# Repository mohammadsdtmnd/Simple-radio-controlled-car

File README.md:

# Simple-radio-controlled-car
Here is the hardware of RC car, including its motor driver through radio, battery pack cell balancer/protector and battery charger
System targer:
1- Two 5V 1.3A Motor drive
2- Series 4 cell battery pack with cell balancer and pack protector
3- Simple USB type C, 4 series cell Li-Ion charger

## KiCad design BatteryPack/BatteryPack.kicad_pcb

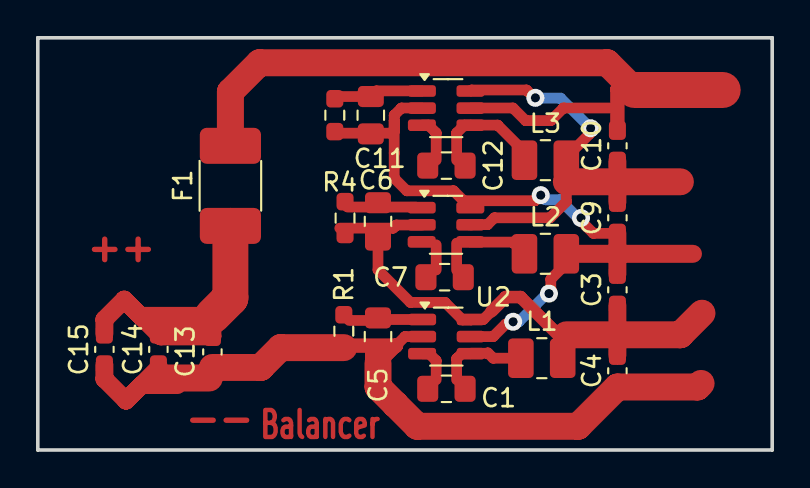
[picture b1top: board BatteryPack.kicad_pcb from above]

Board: 2 copper layers, 40.8 x 22.9 mm, 23 parts (0 on the bottom side), 15 nets.

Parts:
C1, C5, C6, C7, C11, C12: 10nF; C_0805_2012Metric_Pad1.18x1.45mm_HandSolder
C3, C4, C9, C10, C13, C14, C15: 10uF; C_0603_1608Metric_Pad1.08x0.95mm_HandSolder
F1: MF-MSMF150/24X-2; Fuse_1812_4532Metric_Pad1.30x3.40mm_HandSolder
L1, L2, L3: 2.2uH; L_1008_2520Metric_Pad1.43x2.20mm_HandSolder
R1, R4, R6: 27k; R_0603_1608Metric_Pad0.98x0.95mm_HandSolder
U2, U3, U4: ETA3000S2G; SOT-23-6_Handsoldering

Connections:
/cell+: C3.1, C4.2, C6.1, L1.2, R4.2, U2.6 (BATc), U3.2 (BATn)
/pack+: C13.2, C14.2, C15.2, F1.1
/pack-: C4.1, C5.1, C13.1, C14.1, C15.1, R1.2, U2.2 (BATn)
unnamed: C10.2, F1.2, U4.5 (BATP)
unnamed: C9.2, C10.1, L3.2, U3.5 (BATP), U4.6 (BATc)
unnamed: C3.2, C9.1, C11.1, L2.2, R6.2, U2.5 (BATP), U3.6 (BATc), U4.2 (BATn)
unnamed: C1.1, U2.3 (BIAS)
unnamed: C5.2, R1.1, U2.1 (Iset)
unnamed: C1.2, L1.1, U2.4 (SW)
unnamed: C7.1, U3.3 (BIAS)
unnamed: C6.2, R4.1, U3.1 (Iset)
unnamed: C7.2, L2.1, U3.4 (SW)
unnamed: C12.1, U4.3 (BIAS)
unnamed: C11.2, R6.1, U4.1 (Iset)
unnamed: C12.2, L3.1, U4.4 (SW)

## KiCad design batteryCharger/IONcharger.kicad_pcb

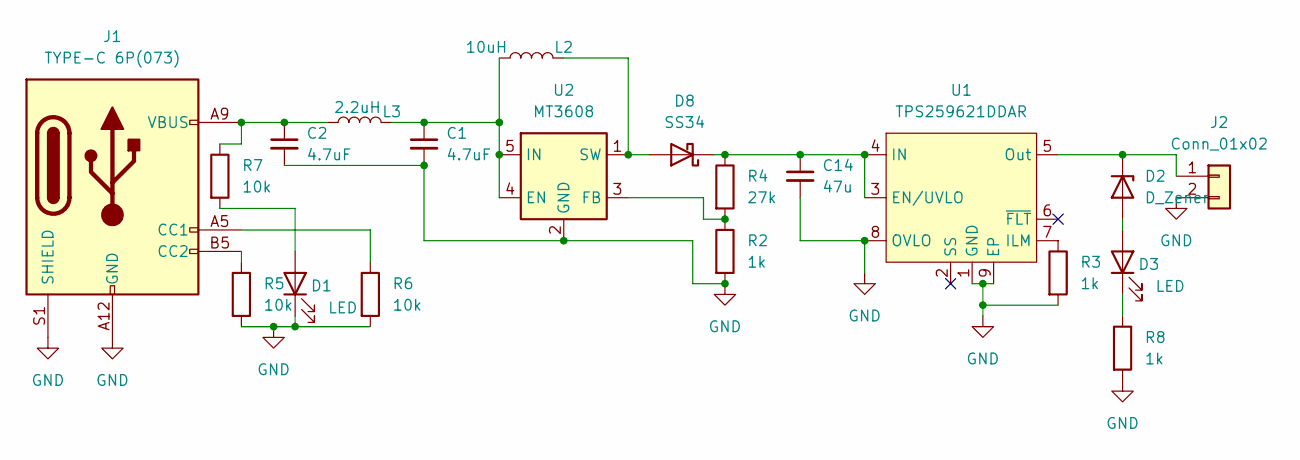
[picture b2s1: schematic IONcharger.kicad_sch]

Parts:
C1, C2: 4.7uF; C_1206_3216Metric_Pad1.33x1.80mm_HandSolder
C14: 47u; C_0805_2012Metric_Pad1.18x1.45mm_HandSolder
D1, D3: LED; LED_0805_2012Metric_Pad1.15x1.40mm_HandSolder
D2: D_Zener; D_SMA_Handsoldering
D8: SS34; D_SMA
J1: TYPE-C 6P(073); USB_C_Receptacle_HRO_TYPE-C-31-M-17
J2: Conn_01x02; SolderWire-0.5sqmm_1x02_P4.6mm_D0.9mm_OD2.1mm
L2: 10uH; L_7.3x7.3_H3.5; Partnumber TMPC0603H-100MG-D
L3: 2.2uH; L_1008_2520Metric_Pad1.43x2.20mm_HandSolder; Partnumber DFE252012F-2R2M=P2
R2, R3, R8: 1k; R_0603_1608Metric_Pad0.98x0.95mm_HandSolder
R4: 27k; R_0603_1608Metric_Pad0.98x0.95mm_HandSolder
R5, R6, R7: 10k; R_0603_1608Metric_Pad0.98x0.95mm_HandSolder
U1: TPS259621DDAR; SOIC-8-1EP_3.9x4.9mm_P1.27mm_EP2.514x3.2mm
U2: MT3608; SOT-23-6

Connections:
GND: C1.2, C2.2, C14.2, D1.1 (K), J1.A12 (GND), J1.B12 (GND), J1.S1 (SHIELD), J2.2, R2.2, R3.2, R5.2, R6.2, R8.2, U1.1 (GND), U1.8 (OVLO), U1.9 (EP), U2.2 (GND)
unnamed: C2.1, J1.A9 (VBUS), J1.B9 (VBUS), L3.1, R7.1
unnamed: D1.2 (A), R7.2
unnamed: D2.2 (A), D3.2 (A)
unnamed: D2.1 (K), J2.1, U1.5 (Out)
unnamed: D3.1 (K), R8.1
unnamed: D8.2 (A), L2.2, U2.1 (SW)
unnamed: C14.1, D8.1 (K), R4.1, U1.3 (EN/UVLO), U1.4 (IN)
unnamed: J1.A5 (CC1), R6.1
unnamed: J1.B5 (CC2), R5.1
unnamed: R3.1, U1.7 (ILM)
unnamed: C1.1, L2.1, L3.2, U2.4 (EN), U2.5 (IN)
unnamed: R2.1, R4.2, U2.3 (FB)

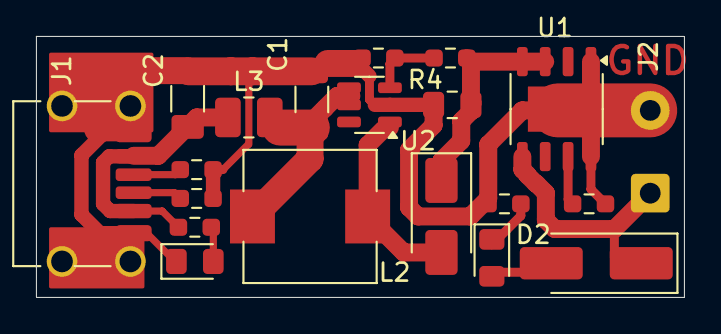
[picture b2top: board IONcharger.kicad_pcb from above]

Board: 2 copper layers, 36.0 x 14.5 mm, 20 parts (0 on the bottom side), 13 nets.

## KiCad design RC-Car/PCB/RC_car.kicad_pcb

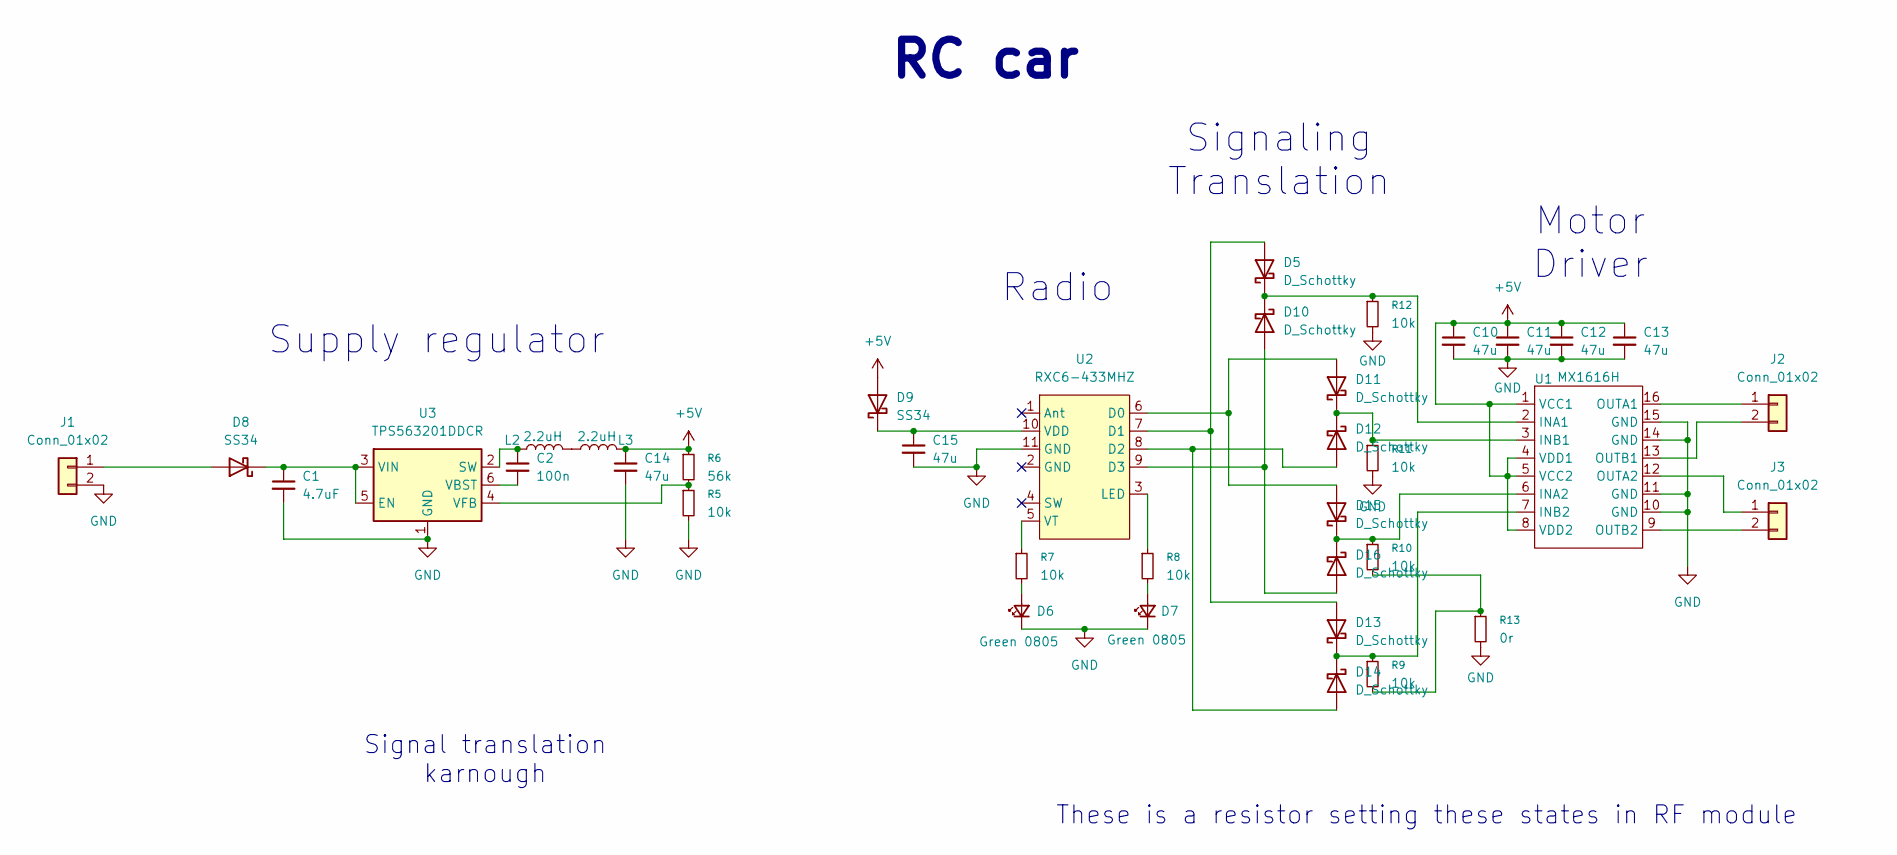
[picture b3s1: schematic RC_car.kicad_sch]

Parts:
C1: 4.7uF; C_1206_3216Metric_Pad1.33x1.80mm_HandSolder
C2: 100n; C_0603_1608Metric_Pad1.08x0.95mm_HandSolder
C10, C11, C12, C13, C14, C15: 47u; C_0805_2012Metric_Pad1.18x1.45mm_HandSolder
D5, D10, D11, D12, D13, D14, D15, D16: D_Schottky; D_SOD-123F_HandSoldering
D6, D7: Green 0805; LED_0805_2012Metric_Pad1.15x1.40mm_HandSolder
D8, D9: SS34; D_SMA
J1, J2, J3: Conn_01x02; SolderWire-0.5sqmm_1x02_P4.6mm_D0.9mm_OD2.1mm
L2, L3: 2.2uH; L_1008_2520Metric_Pad1.43x2.20mm_HandSolder; Partnumber DFE252012F-2R2M=P2
R5, R7, R8, R9, R10, R11, R12: 10k; R_0603_1608Metric_Pad0.98x0.95mm_HandSolder
R6: 56k; R_0603_1608Metric_Pad0.98x0.95mm_HandSolder
R13: 0r; R_1206_3216Metric_Pad1.30x1.75mm_HandSolder
U1: MX1616H; SOP-16_3.9x9.9mm_P1.27mm
U2: RXC6-433MHZ
U3: TPS563201DDCR; SOT-23-6

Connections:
+5V: C10.1, C11.1, C12.1, C13.1, C14.1, D9.2 (A), L3.2, R6.1, U1.1 (VCC1), U1.4 (VDD1), U1.5 (VCC2), U1.8 (VDD2)
GND: C1.2, C10.2, C11.2, C12.2, C13.2, C14.2, C15.2, D6.1 (K), D7.1 (K), J1.2, R5.2, R11.2, R12.2, R13.2, U1.10 (GND), U1.11 (GND), U1.14 (GND), U1.15 (GND), U2.11 (GND), U3.1 (GND)
unnamed: D6.2 (A), R7.2
unnamed: D7.2 (A), R8.2
unnamed: D8.2 (A), J1.1
unnamed: C1.1, D8.1 (K), U3.3 (VIN), U3.5 (EN)
unnamed: C15.1, D9.1 (K), U2.10 (VDD)
unnamed: D10.2 (A), D16.2 (A), U2.9 (D3)
unnamed: D5.1 (K), D10.1 (K), R12.1, U1.2 (INA1)
unnamed: D11.2 (A), D15.2 (A), U2.6 (D0)
unnamed: D11.1 (K), D12.1 (K), R11.1, U1.3 (INB1)
unnamed: D12.2 (A), D14.2 (A), U2.8 (D2)
unnamed: D5.2 (A), D13.2 (A), U2.7 (D1)
unnamed: D13.1 (K), D14.1 (K), R9.1, U1.7 (INB2)
unnamed: D15.1 (K), D16.1 (K), R10.1, U1.6 (INA2)
unnamed: J2.1, U1.16 (OUTA1)
unnamed: J2.2, U1.13 (OUTB1)
unnamed: J3.1, U1.12 (OUTA2)
unnamed: J3.2, U1.9 (OUTB2)
unnamed: L2.2, L3.1
unnamed: R9.2, R10.2, R13.1
unnamed: R8.1, U2.3 (LED)
unnamed: R7.1, U2.5 (VT)
unnamed: C2.1, L2.1, U3.2 (SW)
unnamed: C2.2, U3.6 (VBST)
unnamed: R5.1, R6.2, U3.4 (VFB)

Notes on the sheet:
Signal translation karnough
Motor Driver
RC car
Signaling Translation
These is a resistor setting these states in RF module
Radio
Supply regulator

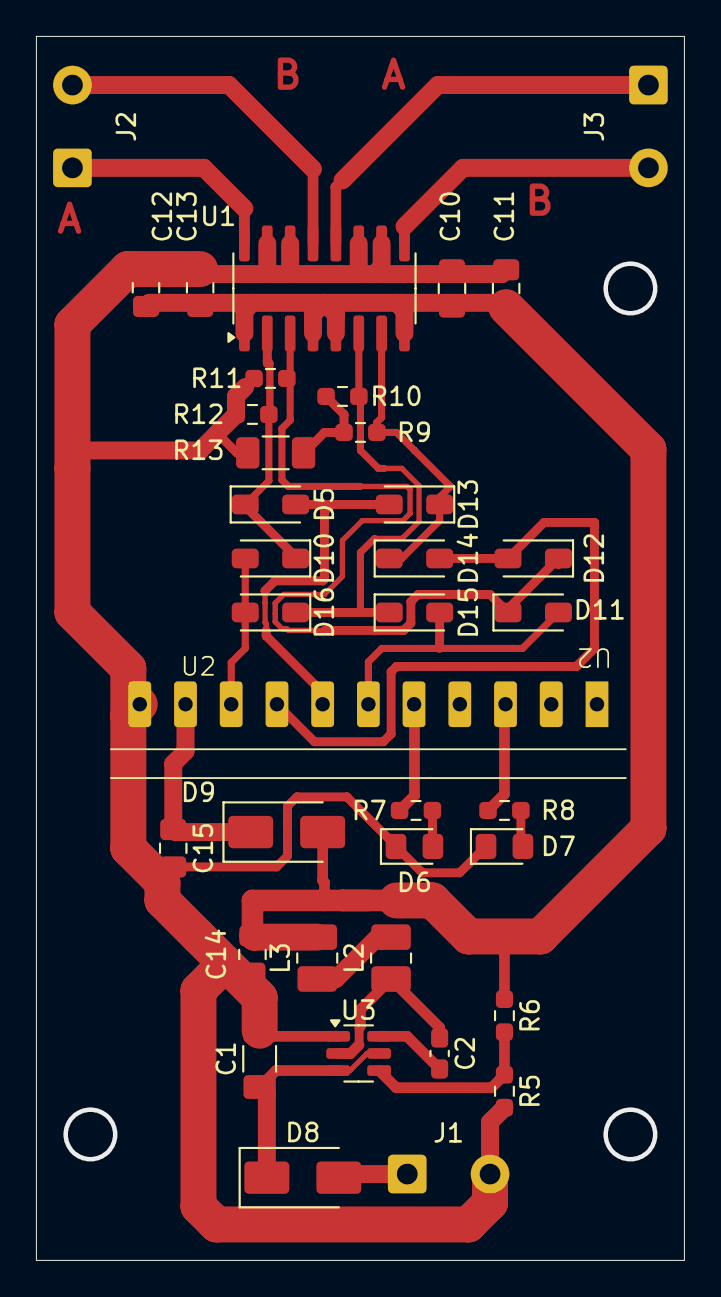
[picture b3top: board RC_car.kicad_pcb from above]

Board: 2 copper layers, 36.0 x 68.0 mm, 37 parts (0 on the bottom side), 26 nets.

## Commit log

2026-01-03 RC-car folder created
2026-01-03 add rc car files
2026-01-04 Create rc-car directory
2026-01-04 Create RC-car PCB directory
2026-01-04 Added pdf of rc-car PCB and schematic
2026-01-04 add pre design files
2026-01-04 add battery pack pcb resources
2026-01-04 create battery charger directory
2026-01-04 Add charger PCB resources
2026-01-04 adding system target
2026-01-05 Create batteryPack directory again
